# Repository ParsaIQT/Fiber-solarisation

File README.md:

# Reduced fibre solarisation in an oxygen-free atmosphere

MSc thesis project: **"Experimental demonstration of reduced fibre solarisation in an oxygen-free atmosphere"**

Thorlabs P3-375PM-FC patch cables (PM-S350-HP, pure-silica core, FC/APC) carry a few mW of 369.5 nm light
(Yb⁺ cooling and detection). They couple very well right after a fresh polish. Their throughput then
falls at a rate that grows with power, at both the input and the output end. This project tests
whether keeping the end faces in an oxygen-free atmosphere halts the degradation, using 3D-printed
enclosures with oxygen absorbers or an inert-gas purge. The experiment is designed to identify the
real cause if oxygen is not it.

## Documents

| Path | What it is |
| --- | --- |
| [`pdf/Fibre-solarisation_MSc-proposal-and-guide.pdf`](pdf/Fibre-solarisation_MSc-proposal-and-guide.pdf) | Full research proposal (Part I), student guide (Part II), appendices (design estimates, draft SOPs, logging spec), ~150 verified references |
| [`pdf/Fibre-solarisation_MSc-proposal-summary.pdf`](pdf/Fibre-solarisation_MSc-proposal-summary.pdf) | 4-page summary |
| `docs/` | LaTeX sources (`proposal.tex`, `summary.tex`, `sections/`, `figures/` in TikZ, `references.bib`, style `fsproposal.sty`) |
| `calc/estimates.py` | Design estimates quoted in Appendix A: end-face intensity, contamination flux, film thickness and heating, gas diffusion in silica, purge, permeation and absorber budgets, optics, statistics |

## Lab hardware

| Path | What it is |
| --- | --- |
| [`laser-pulse-driver/`](laser-pulse-driver/README.md) | TTL-gated 405 nm laser-diode pulse driver (BDR-209) for the photo-ionisation second step during ablation loading: KiCad schematic and 4-layer PCB with JLCPCB assembly files, 3D-printed enclosure, ngspice simulations and an ARTIQ example |

## Main points of the proposal

- **The damage is at the end faces.** Re-polishing restores the throughput, and O₂ cannot diffuse
  into silica at room temperature (nanometres per year). Any oxygen effect must therefore act at the
  surfaces.
- **The literature points both ways.** For hydrocarbon contamination of UV optics, oxygen, and often
  water, is *protective*. This holds for space lasers, UV cavities in ion-trap labs and GaN diodes.
  Under CW light at our intensity, deposits grow fastest at *trace* O₂. For siloxanes from silicones,
  O₂ ≥ 100 ppm has been found to *accelerate* deposits on a 410 nm fibre end face. Particles and
  restructuring of the silica surface itself (seen at 405 nm) are further candidates.
- **The decisive test** runs identical fibres in parallel in ambient air, clean dry synthetic air,
  clean dry N₂ and a sealed absorber cell. Only the air/N₂ pair differs in O₂ alone. Later arms add an
  O₂ dose–response, humidity, polymer and silicone challenges, and a crossed input/output design.
- **Practical outcome:** a qualified 3D-printed cell (CAD, BOM, SOPs) that holds < 100 ppm O₂ for months,
  tested on a working 369.5 nm link. If the atmosphere turns out not to be the cause, the fall-back is
  a recommendation for end-face engineering (end caps, H₂-loaded or hollow-core fibre).

## Building

Requires TeX Live (with `biber` and `latexmk`) and Python 3 (standard library only).

```sh
make            # builds both PDFs into pdf/
make estimates  # prints the numbers used in Appendix A
make clean
```

The `docs/` folder can also be uploaded to Overleaf as is (compiler: pdfLaTeX, bibliography: Biber).

## Status

Version 1.0 (18 October 2026): draft for discussion between the supervisor and the student. Names are
placeholders. Prices are US list prices or rough estimates; replace them with quotes.

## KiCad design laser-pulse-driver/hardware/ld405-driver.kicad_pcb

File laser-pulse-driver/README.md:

# LD405 – pulsed driver for a 405 nm (BDR-209) photo-ionisation laser diode

A bench-top, TTL-gated constant-current driver for a 405 nm laser diode used as
the second (ionising) step of a two-photon REMPI scheme during ablation loading.
An ARTIQ TTL line switches the diode between a low *idle* current (adjustable
5–104 mA: below threshold, or just above it for a dim alignment beam) and a
*pulse* current (adjustable 0–600 mA, or 0–700 mA with jumper JP1) for as long
as the TTL is high, e.g. 100 µs per ablation shot.

| | |
|---|---|
| Output | high-side current source, diode cathode at ground (Thorlabs "CG" DB9 pin-out) |
| Pulse current | 0–600 mA (PULSE knob), 0–700 mA with JP1 bridged; over-current trip at ~800 mA |
| Idle current | 5–104 mA (IDLE knob) whenever the TTL input is low or unconnected |
| Timing (simulated, 0.5–2.5 m cable) | ~0.7 µs delay, 4–6 µs 10–90 % rise, no overshoot, 1 % settled in ≤ 12 µs, ~7 µs fall |
| TTL input | BNC, 10 kΩ to ground, Schmitt trigger: high ≥ 2.0 V, low ≤ 0.5 V (≥ 0.4 V hysteresis); series 220 Ω + Schottky clamps to the rails. 3.3 V or 5 V TTL from ARTIQ (Kasli DIO-BNC / DIO-SMA) works directly |
| Monitors | I MON (measured diode current) and SET MON (pulse setpoint), both 1 V/A into high impedance (0.5 V/A into 50 Ω) |
| Compliance | ≥ 7 V across the diode at 700 mA (BDR-209 needs ~5–6 V) |
| Protection | output shorted by a relay and a MOSFET crowbar whenever disarmed; soft start (80 ms); over-current, open-circuit/compliance and over-temperature (85 °C) trips; two interlocks (3.5 mm jack + DB9 loop); fault latch that needs a deliberate re-arm; no auto-start after power-up |
| Supply | 9 V DC, ≥ 1.5 A (5.5/2.1 mm plug, centre positive); reverse-polarity, over-voltage and PTC fuse protection |
| Board / box | 160 × 100 mm 4-layer PCB (Eurocard), 3D-printed case 181 × 108 × 32 mm |

Design notes, simulation results and the protection logic are in
[docs/design-notes.md](docs/design-notes.md); the ARTIQ example is in
[artiq/ld405_pulse.py](artiq/ld405_pulse.py).

> **Class 4 laser.** A BDR-209 at these currents emits close to 1 W at 405 nm.
> Wear OD ≥ 4 eyewear rated for 405 nm whenever the diode is connected and
> armed, enclose the beam path, and use the interlock inputs (see *Safety*).

---

## 1. What to order, and where (UK)

Everything below ships to the UK. JLCPCB adds UK VAT at checkout for orders
up to £135; above that the courier (DHL/UPS) collects import VAT on delivery.

### 1.1 Assembled boards – JLCPCB (jlcpcb.com)

Upload these three files from [`hardware/fab/`](hardware/fab/):

| JLCPCB field | file |
|---|---|
| Gerber file (PCB order) | `ld405-driver_gerbers_jlcpcb.zip` |
| BOM (PCB Assembly step) | `ld405-driver_bom_jlcpcb.csv` |
| CPL / pick-and-place | `ld405-driver_cpl_jlcpcb.csv` |

PCB options (everything else at default):

* Layers **4**, dimensions 160 × 100 mm (read from the Gerbers), thickness **1.6 mm**,
  outer copper 1 oz, inner 0.5 oz, any colour, surface finish *LeadFree HASL*
  (or *ENIG* for the flattest pads; leaded HASL also works but puts lead on the board).
* Via covering: *Plugged* (JLCPCB no longer offers *Tented* on 4-layer boards;
  plugged vias are covered just the same, which is what the design needs).
  Min via hole size: *0.3 mm (0.4/0.45 mm)*; the board's vias are 0.3 mm drill, 0.6 mm pad.
* Quantity: 5 boards, of which **2 assembled** (one spare).

The price shown at this point covers the bare boards only. Parts and assembly
are priced after the next step.

PCB Assembly options (switch on *PCB Assembly* below *Advanced Options*):

* **Standard PCBA**, assemble **top side** only, PCBA quantity **2**, tooling
  holes added by JLCPCB. The connectors, pots and the toggle switch are
  through-hole; JLCPCB hand-solders them as part of Standard PCBA. Confirm
  *"Parts placement"* so an engineer checks it.
* Click *Next*, upload the BOM and CPL, check that every line matched a part,
  then *Next* to the placement preview; the final price (parts, assembly,
  extended-part fees) appears after that.
* After the BOM/CPL upload JLCPCB shows a placement preview. Check that the
  pin-1/polarity marks agree for: U1–U14, Q1–Q11, diodes D1–D16, the LEDs
  (D3, D8, D12, D16 – lenses must face the board edge), C1/C2 (electrolytic)
  and K1. The CPL already contains the usual KiCad→JLC rotation offsets
  (SOT-23 +180°, SOIC +270°, electrolytics +180°), offsets for the panel
  parts (BNCs +90°, pots, toggle and DE-9 +270°) and per-part corrections
  found in the preview (C1/C2, K1, Q2, D10). Compare the pink markers with
  `docs/review/jlc_markers_overview.png`. In the 3D preview the BNC
  bayonets, pot shafts and toggle lever must stick out over the front edge,
  and the DE-9, 3.5 mm jack and DC jack must open over the rear edge; rotate
  anything that still looks wrong.
* All 69 BOM lines were in stock at JLCPCB/LCSC on 28 Oct 2026 (32 are
  "extended" parts, which carry JLCPCB's per-part setup fee). Expect roughly
  £200–300 for 2 assembled boards + 3 bare boards including shipping; the
  parts themselves are ~£25 per board.
* JP1 (700 mA range) is a solder jumper and is **left open** by JLCPCB.

### 1.2 Enclosure – 3D print (JLC3DP, any UK print service, or in-house)

STL files in [`enclosure/stl/`](enclosure/stl/), already in print orientation:

| file | qty | notes |
|---|---|---|
| `ld405_base.stl` | 1 | floor, side walls, PCB standoffs, lid posts |
| `ld405_lid.stl` | 1 | printed top-side down (engraved laser warning) |
| `ld405_front_panel.stl` | 1 | BNC/pot/switch/LED holes, engraved labels |
| `ld405_rear_panel.stl` | 1 | DB9, interlock jack and DC jack |

* **JLC3DP** (same JLCPCB account, "3D Printing" tab): *MJF PA12 nylon*
  (black) is strong, dimensionally accurate and needs no tuning. Add it to the
  PCB order to share shipping. Its thin-wall heatmap should show nothing under
  1.2 mm except inside the engraved lettering (the narrow ridges between
  letters), which is normal for engraved text.
* UK alternatives: Protolabs (Telford, MJF/SLS), 3DPrintUK (London, SLS nylon),
  or the Craftcloud marketplace.
* In-house FDM: PETG or ASA, 0.2 mm layers, 4 perimeters, 30 % infill, no
  supports needed. Bed ≥ 185 × 110 mm.

The OpenSCAD source [`enclosure/ld405_enclosure.scad`](enclosure/ld405_enclosure.scad)
is generated from the board placement (`tools/gen_enclosure.py`), so the
holes follow the connectors if the layout changes.

### 1.3 Power supply and parts from RS Components / Farnell / CPC

| item | part | notes |
|---|---|---|
| 9 V DC supply | **Mean Well GST25A09-P1J** (9 V, 2.5 A, 5.5/2.1 mm plug, centre +) | desktop adapter with an IEC C14 inlet; any 9 V ≥ 1.5 A regulated supply with a 5.5/2.1 mm centre-positive plug works. RS, Farnell and CPC all stock it. |
| mains lead | UK plug → IEC C13 ("kettle lead"), 2 m | the 240 V socket within 2 m is enough |
| DB9 plug for the diode cable | DE-9 **male** solder-cup plug + metal hood with 4-40 jack screws | e.g. Amphenol/TE/Harting, any brand |
| diode cable | 2-core screened cable or a twisted pair, ≤ 2.5 m | keep the pair twisted to the diode |
| interlock plug | 3.5 mm **mono** jack plug | shorting plug, or wired to a door/enclosure interlock |
| knobs | 2 × knob for **6 mm D (flatted) shaft**, 15 mm shaft length | |
| screws | 4 × M3×16 countersunk + 4 × M3 nut (PCB); 4 × M3×10 countersunk + 4 × M3 nut (lid) | stainless A2 |
| feet | 4 × self-adhesive rubber feet, ≤ 10 mm diameter | |

The BNC nuts and washers come with the connectors; the pots normally come with
an M9×0.75 nut and washer (buy two if not).

### 1.4 Laser diode – DTR's Laser Shop

* *900 mW 405 nm Blu-ray BDR-209 laser diode in copper module with leads*
  (optionally with the *G-2 glass lens* for collimation). DTR does not publish
  a datasheet; users report ~0.8–1 W at ~500–650 mA with ~5–6 V forward
  voltage, which this driver covers with margin. Calibrate the power yourself
  (section 4).
* Clamp the copper module in a heat-sinking holder. The diode case must not be
  connected to anything except through the DB9 cable.

### 1.5 Laser safety

Eyewear rated OD ≥ 4 at 405 nm for every person in the room (Thorlabs,
Laservision, Uvex and others sell suitable orange/amber filters), plus a beam
enclosure and beam dumps appropriate for a Class 4 source.

---

## 2. Assembly (about 30 minutes)

1. **Diode cable.** Solder the DE-9 male plug: **pin 8 → diode anode (+, red)**,
   **pin 3 → diode cathode (−, black)**, and a **wire link from pin 1 to pin 5**
   inside the hood (cable interlock: unplugging the cable trips the driver).
   Screen (if any) to pin 3 at the driver end only.
2. **Interlock plug.** Short tip to sleeve in a 3.5 mm mono plug, or wire it
   to normally-closed contacts of your enclosure/door interlock.
3. **Enclosure.** Push 4 × M3 nuts into the side slots at the tops of the
   lid posts. Fit the front panel onto the board (BNC nuts and washers on the
   outside; pot nuts on the outside, the pot's small anti-rotation lug sits in
   the notch below its hole), and the rear panel over the DB9 shell. Lower
   board + panels into the base so the panels drop into their grooves, then fix
   the board with 4 × M3×16 countersunk screws from below and nuts on top.
   Fit the knobs, put the lid on, 4 × M3×10 countersunk screws.

The ENABLE toggle is held by the board only (its bushing just passes through
the panel), so operate it gently.

---

## 3. Front and rear panel

| front | function |
|---|---|
| **TTL IN** (BNC) | high = pulse current, low/unconnected = idle current |
| **I MON** (BNC) | measured diode current, 1 V/A (high-Z scope input) |
| **SET MON** (BNC) | pulse setpoint, 1 V/A – shows what a pulse will deliver before you fire |
| **PULSE** | pulse current 0 → full scale (600 mA, or 700 mA with JP1) |
| **IDLE** | idle current 5 → 104 mA |
| **ENABLE** | arm / disarm, and reset after a fault (toggle off → on) |
| LEDs | POWER (green) · ARMED (yellow: relay open, current source enabled) · EMISSION (blue: diode current > ~18 mA, stretched so 100 µs pulses are visible) · FAULT (red, latched) |

| rear | |
|---|---|
| **LD OUT** (DE-9 female) | 8 = anode, 3 = cathode/ground, 1–5 = interlock loop (Thorlabs CG compatible) |
| **INTERLOCK** (3.5 mm) | must be closed (tip–sleeve shorted) to arm |
| **9V DC** | 9 V, ≥ 1.5 A, centre positive |

Arming sequence: after power-up the driver is always in FAULT (no automatic
start). With both interlocks closed, switch ENABLE off → on: the relay opens
the output short, ~20 ms later the current source starts and ramps to the idle
current over ~80 ms. Any fault (over-current, open diode/compliance,
over-temperature, interlock open) immediately shorts and crowbars the output
and latches FAULT until ENABLE is switched off and on again.

---

## 4. First power-up and calibration

1. **Without the diode**: plug in the DB9 cable with a **dummy load** instead
   of the diode – e.g. 5 × 1N5408 (or 1N4007) in series plus a 1 Ω 2 W
   resistor (≈ 5–6 V at 0.6 A, like the laser diode; pulsed use only) – and
   the interlock plug. Turn both knobs fully anticlockwise.
2. Power up: POWER on, FAULT on. ENABLE off → on: ARMED on, FAULT off.
3. Scope on I MON (1 V/A). Turn IDLE: the trace moves between ~5 and ~104 mV.
4. Drive TTL IN with 100 µs pulses at ≤ 10 Hz (section 5). Turn PULSE up:
   I MON shows the pulses; SET MON shows the level a pulse will reach.
   Check the pulse at full scale (≈ 600 mV on I MON) is flat with no ringing.
5. Optional 700 mA range: bridge solder jumper **JP1** (near U2/REF3030).
6. Disconnect one lead of the dummy load at the far end, leaving the DB9
   plugged in: FAULT must latch (open-circuit detection). Unplugging the DB9
   itself must also latch FAULT (cable interlock). Set both knobs to minimum,
   **disarm**, connect the diode, then arm.
7. Calibrate optical power with a thermal power meter: at a known duty cycle
   *D* the meter reads *P̄ ≈ P_peak · D* (e.g. 100 µs at 100 Hz, D = 1 %), or
   use a fast photodiode for the pulse shape. Increase PULSE slowly; read the
   current on I MON and note the knob position for your target peak power
   (~900 mW). Do not exceed the diode's current rating.

Duty cycle: the driver itself is fine at any duty cycle up to a few % at full
current (the pass transistor is heat-sunk into the board and the 85 °C
trip protects it); limit the duty cycle further for the diode's sake.

---

## 5. Using it from ARTIQ

Connect a Kasli TTL output (DIO-BNC/-SMA) to **TTL IN**. TTL high = pulse.
The current needs ~1 µs to start rising and ~10 µs to settle to 1 %, so open
the pulse ~10–15 µs before you need full power. [`artiq/ld405_pulse.py`](artiq/ld405_pulse.py)
fires the ablation trigger inside a 100 µs 405 nm pulse:

```python
with parallel:
    self.ttl_ld405.pulse(self.pulse_width)          # 405 nm REMPI 2nd step
    with sequential:
        delay(self.lead)                            # ~15 us head start
        self.ttl_ablation.pulse(self.ablation_width)
```

Tip: setting IDLE just above threshold gives a dim continuous 405 nm beam for
aligning onto the trap without firing pulses.

---

## 6. Repository layout

| path | contents |
|---|---|
| `hardware/` | KiCad 9 project: schematic, 4-layer PCB, custom footprints (`lib/ld405.pretty`) |
| `hardware/fab/` | manufacturing outputs (Gerbers, BOM, CPL), schematic + assembly PDFs, renders |
| `enclosure/` | OpenSCAD source, STL files, preview images |
| `artiq/` | ARTIQ experiment for ablation loading with the pulsed 405 nm laser |
| `sim/` | ngspice testbench and corner simulations (`get_models.sh` fetches the vendor models) |
| `docs/` | design notes, simulation plots and the design-review renders (`docs/review/`) |
| `review_package/` | for an outside reviewer: `LD405_design_review.pdf` (design review document with schematic) and `LD405_review_pack.zip` (that PDF plus KiCad project, JLCPCB files, layer plots, ERC/DRC reports, simulation, enclosure and review renders) |
| `tools/` | the generators: everything in `hardware/`, `hardware/fab/` and `enclosure/` is produced by these scripts |

Regenerating from source (KiCad 9 with its Python module, numpy, scipy, poppler,
matplotlib, gcc, OpenSCAD, ngspice):

```sh
cd tools
python3 gen_3d.py              # simple 3D models for parts without a KiCad model
python3 gen_fp.py              # custom footprints
python3 gen_sch.py             # schematic (ERC clean)
python3 gen_pcb.py --route     # placement, routing, zones, DRC-clean board
python3 export_fab.py          # Gerbers, drill, BOM, CPL, PDFs, renders
python3 gen_enclosure.py       # OpenSCAD model and STLs
python3 review.py              # review renders in docs/review/
cd ../sim && ./get_models.sh && python3 run_sims.py
cd ../tools && python3 make_review_pack.py   # review_package/ (needs node + Playwright for the PDF)
```

`design.py` is the single source of truth for parts, values, LCSC numbers and
connections; `placement.py` holds the component positions.

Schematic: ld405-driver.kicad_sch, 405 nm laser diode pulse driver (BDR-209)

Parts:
C1, C2: 220uF 25V; CP_Elec_8x10.5; MPN RVT1E221M0810; LCSC C72497
C3, C4, C7, C11: 10uF; C_0805_2012Metric; MPN CL21A106KAYNNNE; LCSC C15850
C5, C8, C13, C14, C16, C17, C18, C20, C21, C22, C23, C24, C25, C26, C34, C40, C41: 100nF; C_0603_1608Metric; MPN CC0603KRX7R9BB104; LCSC C14663
C6, C9, C10, C19: 1uF; C_0603_1608Metric; MPN CL10A105KB8NNNC; LCSC C15849
C12, C31: 220pF C0G; C_0603_1608Metric; MPN GCM1885C2A221JA16D; LCSC C388907
C15, C30, C33: 100pF C0G; C_0603_1608Metric; MPN CL10C101JB8NNNC; LCSC C14858
C32: 47nF; C_0603_1608Metric; MPN CL10B473KB8NNNC; LCSC C1622
C42: 10nF; C_0603_1608Metric; MPN 0603B103K500NT; LCSC C57112
C43: 2.2uF; C_0603_1608Metric; MPN CL10A225KO8NNNC; LCSC C23630
C44: 1nF; C_0603_1608Metric; MPN CL10B102KB8NNNC; LCSC C1588
C45: 220nF; C_0603_1608Metric; MPN CL10B224KA8NNNC; LCSC C21120
D1: BZT52C10; D_SOD-123; MPN BZT52C10; LCSC C19077408
D2: SMAJ13A; D_SMA; MPN SMAJ13A; LCSC C19077533
D3: POWER green; LED_SideView_LiteOn_LTST-S220; MPN LTST-S220TGKT; LCSC C160470
D4: BAT54S; SOT-23; MPN BAT54S; LCSC C7420333
D5, D13, D14, D15: 1N4148WS; D_SOD-323; MPN 1N4148WS; LCSC C2128
D6: SS34; D_SMA; MPN SS34; LCSC C8678
D7: SMAJ12A; D_SMA; MPN SMAJ12A; LCSC C19077531
D8: EMISSION blue; LED_SideView_LiteOn_LTST-S220; MPN LTST-S220TBKT; LCSC C160471
D10: BAT54A; SOT-23; MPN BAT54A; LCSC C7502690
D12: FAULT red; LED_SideView_LiteOn_LTST-S220; MPN LTST-S220KRKT; LCSC C284935
D16: ARMED yellow; LED_SideView_LiteOn_LTST-S220; MPN LTST-S220KSKT; LCSC C160468
F1: 2A PTC; Fuse_1812_4532Metric; MPN BSMD1812-200-30V; LCSC C960026
H1, H2, H3, H4: M3; MountingHole_3.2mm_M3_Pad_Via
J1: 9V DC IN; BarrelJack_DC-005_Horizontal; MPN DC-005-5A-2.0; LCSC C381116
J2: TTL IN; BNC_DOSIN_801-0080_Horizontal; MPN DOSIN-801-0080; LCSC C521219
J3: SET MON; BNC_DOSIN_801-0080_Horizontal; MPN DOSIN-801-0080; LCSC C521219
J4: I MON; BNC_DOSIN_801-0080_Horizontal; MPN DOSIN-801-0080; LCSC C521219
J5: LD OUT; DSUB-9_Socket_Horizontal_P2.77x2.84mm_EdgePinOffset7.70mm_H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; MPN DS1037-09FNAKT74-0CC; LCSC C75749
J6: INTERLOCK; Jack_3.5mm_KoreanHropartsElec_PJ-320D-4A_Horizontal; MPN PJ-320D; LCSC C431535
JP1: I_MAX 700mA; SolderJumper-2_P1.3mm_Open_RoundedPad1.0x1.5mm
K1: G6K-2F-Y 5V; Relay_DPDT_Omron_G6K-2F-Y; MPN G6K-2F-Y-TR DC5; LCSC C47190
NT1, NT2: NetTie; NetTie-2_SMD_Pad0.5mm
Q1, Q6, Q7, Q11: AO3401A; SOT-23; MPN AO3401A; LCSC C15127
Q2: IRFR9024N; TO-252-2; MPN IRFR9024NTRPBF; LCSC C2585
Q3, Q4, Q5, Q8, Q9: 2N7002; SOT-23; MPN 2N7002; LCSC C8545
Q10: AO3400A; SOT-23; MPN AO3400A; LCSC C20917
R1, R15, R36, R37, R39, R43, R53, R54, R59, R78, R79: 100k; R_0603_1608Metric; LCSC C25803
R2: 2.2k; R_0603_1608Metric; LCSC C4190
R10: 10k 0.1%; R_0603_1608Metric; MPN RT0603BRD0710KL; LCSC C95204
R11: 40.2k 0.1%; R_0603_1608Metric; MPN TD03G4022BT; LCSC C667101
R12: 4.02k; R_0603_1608Metric; LCSC C23040
R13, R30, R34, R42: 100; R_0603_1608Metric; LCSC C22775
R16, R17, R33, R62, R81, R82: 1k; R_0603_1608Metric; LCSC C21190
R18, R31, R45: 3k 0.1%; R_0603_1608Metric; MPN RT0603BRD073KL; LCSC C136963
R19, R46: 1k 0.1%; R_0603_1608Metric; MPN RT0603BRD071KL; LCSC C110776
R20, R47: 49.9; R_0603_1608Metric; LCSC C23185
R21: 220; R_0603_1608Metric; LCSC C22962
R22, R35, R50, R56, R70, R73: 10k; R_0603_1608Metric; LCSC C25804
R32: 150 0.1%; R_0603_1608Metric; MPN AR03BTCX1500; LCSC C319859
R38, R48: 47k; R_0603_1608Metric; LCSC C25819
R40: 0.2; R_2512_6332Metric; MPN RLP25FEER200; LCSC C459674
R41: 1.0; R_2512_6332Metric; MPN 25121WF100KT4E; LCSC C11254
R44: 22; R_0805_2012Metric; LCSC C17561
R51: 18k; R_0603_1608Metric; LCSC C25810
R52: 300k; R_0603_1608Metric; LCSC C23024
R55: 11k; R_0603_1608Metric; LCSC C25950
R60: 1.5k; R_0603_1608Metric; LCSC C22843
R61: 1M; R_0603_1608Metric; LCSC C22935
R72: 4.7k; R_0603_1608Metric; LCSC C23162
R77: 3.3k; R_0603_1608Metric; LCSC C22978
RT1: 10k B3950; R_0603_1608Metric; MPN SDNT1608X103F3950FTF; LCSC C279936
RV1: PULSE 20k; Potentiometer_Alps_RK09L_Single_Horizontal; MPN RK09L112003P; LCSC C470444
RV2: IDLE 20k; Potentiometer_Alps_RK09L_Single_Horizontal; MPN RK09L112003P; LCSC C470444
SW1: ENABLE; Toggle_Dailywell_1MS1T2B4M7QES; MPN 1MS1T2B4M7QES; LCSC C496157
U1: L78M05ABDT; TO-252-2; MPN L78M05ABDT-TR; LCSC C58069
U2: REF3030; SOT-23; MPN REF3030AIDBZR; LCSC C38423
U3, U4, U10: TLV9062; SOIC-8_3.9x4.9mm_P1.27mm; MPN TLV9062IDR; LCSC C398355
U5: SN74LVC1G3157; SOT-23-6; MPN SN74LVC1G3157DBVR; LCSC C10426
U7: OPA2192; SOIC-8_3.9x4.9mm_P1.27mm; MPN OPA2192IDR; LCSC C110074
U8: INA180A1; SOT-23-5; MPN INA180A1IDBVR; LCSC C122228
U11: LM2901; SOIC-14_3.9x8.7mm_P1.27mm; MPN LM2901DR; LCSC C7932
U12: 74HC14; SOIC-14_3.9x8.7mm_P1.27mm; MPN 74HC14D; LCSC C5605
U13: 74HC132; SOIC-14_3.9x8.7mm_P1.27mm; MPN SN74HC132DR; LCSC C350560
U14: 74AHCT1G14; SOT-23-5; MPN SN74AHCT1G14DBVR; LCSC C55250

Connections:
+5V: C7.1, C8.1, C10.1, C13.1, C14.1, C16.1, C17.1, C20.1, C21.1, C22.1, C25.1, C26.1, D4.2 (K), D5.1 (K), D13.1 (K), K1.1, Q11.2 (S), R2.1, R50.1, R54.1, R56.1, R59.1, R61.1, R70.1, R72.1, R73.1, R77.1, R78.1, U1.3 (VO), U2.1 (IN), U3.8 (V+), U4.8 (V+), U5.5 (VCC), U8.5 (V+), U10.8 (V+), U11.3 (V+), U12.14 (VCC), U13.14 (VCC), U14.5 (VCC)
CB_G: Q10.1 (G), R42.2, R43.1
CLAMP_G: Q6.1 (G), Q7.3 (D), R37.2, R38.1
CMP_REF: C23.1, R54.2, R55.1, U11.6 (-), U11.10 (-)
DB9_IL: C42.1, J5.1, R77.2, U12.5
DB9_OK: D10.2, U12.6
DIS_LOOP: Q3.1 (G), Q5.1 (G), R42.1, U12.8, U12.11
EA_N: C31.1, R33.2, R36.2, U7.2 (-)
EA_OUT: C31.2, R34.1, U7.1
EMI_RC: C34.1, Q11.1 (G), R61.2, U11.14
EM_REF: R59.2, R60.1, U11.9 (+)
EN_DLY: C45.1, D15.2 (A), R79.2, U12.9
EN_LOOP: Q8.1 (G), U12.10
EN_ON: U12.2, U13.4, U13.9
EN_REQ: D15.1 (K), Q9.1 (G), R79.1, R82.1, U13.11
EN_REQ_N: U13.8, U13.12, U13.13
EN_SW: C40.1, R70.2, SW1.1 (A), U12.1
FAULT: R81.1, U13.3, U13.5
FAULT_N: U13.2, U13.6, U13.10
GATE: Q2.1 (G), Q6.3 (D), R34.2, R35.1, R52.1
GATE_N: U5.6, U14.4
GND: C1.2, C2.2, C3.2, C4.2, C5.2, C6.2, C7.2, C8.2, C9.2, C10.2, C11.2, C12.2, C13.2, C14.2, C15.2, C16.2, C17.2, C18.2, C19.2, C20.2, C21.2, C22.2, C23.2, C24.2, C25.2, C26.2, C32.2, C33.2, C34.2, C40.2, C41.2, C42.2, C43.2, C44.2, C45.2, D2.2 (A2), D3.1 (K), D4.1 (A), D6.2 (A), D7.2 (A2), D8.1 (K), D12.1 (K), D16.1 (K), H1.1, H2.1, H3.1, H4.1, J1.2, J1.3, J2.2 (Ext), J3.2 (Ext), J4.2 (Ext), J5.0 (PAD), J5.3, J5.5, J6.S, K1.2, K1.7, Q3.2 (S), Q5.2 (S), Q8.2 (S), Q9.2 (S), Q10.2 (S), R1.2, R11.2, R16.2, R19.2, R22.2, R31.2, R38.2, R43.2, R46.2, R51.2, R53.2, R55.2, R60.2, RT1.2, RV1.1, SW1.2 (B), U1.2 (GND), U2.3 (GND), U3.4 (V-), U4.4 (V-), U5.2 (GND), U7.4 (V-), U8.2 (GND), U10.4 (V-), U10.5 (+), U11.12 (V-), U12.7 (GND), U12.13, U13.7 (GND), U14.3 (GND)
G_DIV: C33.1, R52.2, R53.1, U11.7 (+)
IDLE_BOT: R16.1, RV2.1
IDLE_TOP: R15.2, RV2.3
IMON: J4.1 (In), R47.2
IMON_INT: R45.1, U8.1, U11.4 (-), U11.8 (-)
IMON_OUT: R47.1, U10.1, U10.2 (-)
IM_DIV: R45.2, R46.1, U10.3 (+)
JP1_B: JP1.2 (B), R12.1
LD_OUT: D6.1 (K), D7.1 (A1), J5.8, K1.3, K1.6, Q2.2 (D), Q10.3 (D), R44.1
LED_ARM: D16.2 (A), R82.2
LED_EMI: D8.2 (A), R62.2
LED_FLT: D12.2 (A), R81.2
LED_PWR: D3.2 (A), R2.2
LS_G: Q4.1 (G), R30.2
LS_GO: R30.1, U7.7
LS_S: Q4.2 (S), R31.1, U7.6 (-)
NTC_N: C24.1, R56.2, RT1.1, U11.11 (+)
OC_REF: R50.2, R51.1, U11.5 (+)
POR_RC: C43.1, D13.2 (A), D14.1 (K), R78.2
Q1_G: D1.2 (A), Q1.1 (G), R1.1
Q5_D: Q5.3 (D), R36.1
Q8_D: Q8.3 (D), R48.2
Q11_D: Q11.3 (D), R62.1
REF_N: C30.2, Q4.3 (D), R32.2, U7.3 (+)
REL_G: Q7.1 (G), R39.2, R48.1
REM_N: C41.1, J6.T, R72.2, U12.3
REM_OK: D10.1, U12.4
RLY_N: D5.2 (A), K1.8, Q9.3 (D)
SETMON: J3.1 (In), R20.2
SETMON_OUT: R20.1, U4.6 (-), U4.7
SM_DIV: R18.2, R19.1, U4.5 (+)
SNUB: C32.1, R44.2
SRC_D: Q2.3 (S), R41.2
SRC_K: NT2.1, R40.2, R41.1
SRC_SNS: NT2.2, R33.1, U8.4 (-)
SS_D: Q3.3 (D), R13.1
S_N: C44.1, D10.3, D14.2 (A), R73.2, U11.1, U11.2, U11.13, U13.1
TTL_BNC: J2.1 (In), R21.1, R22.1
TTL_PROT: C15.1, D4.3 (COM), R21.2, U14.2
U10B_OUT: U10.6 (-), U10.7
VFS: R15.1, RV1.3, U3.1, U3.2 (-)
VFS_RAW: C11.1, R10.2, R11.1, R12.2, R13.2, U3.3 (+)
VI: U4.1, U4.2 (-), U5.1
VIN: C1.1, C2.1, C3.1, C4.1, C5.1, C6.1, C18.1, C19.1, D1.1 (K), D2.1 (A1), NT1.1, Q1.2 (S), Q6.2 (S), Q7.2 (S), R35.2, R37.1, R39.1, R40.1, U1.1 (VI), U7.8 (V+)
VIN_F: F1.2, Q1.3 (D)
VIN_RAW: F1.1, J1.1
VIN_SNS: C30.1, NT1.2, R32.1, U8.3 (+)
VI_W: RV2.2, U4.3 (+)
VP: R18.1, U3.6 (-), U3.7, U5.3
VP_W: RV1.2, U3.5 (+)
VREF: C9.1, JP1.1 (A), R10.1, U2.2 (OUT)
VSP: C12.1, R17.2, U7.5 (+)
VSP_MUX: R17.1, U5.4

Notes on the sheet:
1 POWER INPUT, 5 V AND 3.000 V REFERENCE
9 V / >=1.5 A desktop adapter (5.5/2.1 mm, centre +).
Q1 = reverse-polarity protection, F1 = resettable fuse, D2 = TVS.
2 SETPOINT, SOFT START AND TTL GATING (scale 4 V/A)
VFS = 2.40 V = 600 mA full scale (JP1 closed: 2.80 V = 700 mA).
C11 + R10||R11 give an 80 ms soft start; Q3 discharges it when disabled.
U5 selects PULSE (TTL high) or IDLE (TTL low, 5..104 mA).
3 TTL INPUT (BNC, 10 k to GND, 3.3/5 V logic)
Schmitt trigger with TTL thresholds; unconnected input = IDLE.
4 HIGH-SIDE CURRENT SOURCE (laser cathode at GND)
I_LD = VSP x (R32/R31) / R40 = VSP / 4 V/A.
U7A error amp senses R40 directly (Kelvin via NT1/NT2); R41 degenerates Q2.
Q6 clamps Q2 off unless EN_LOOP is high (fail-safe, Q7/Q8 release it).
Q5 forces U7A high while disabled so the integrator cannot wind up.
5 OUTPUT, SHORTING RELAY AND CROWBAR
K1 NC contacts short the laser whenever the driver is not armed or unpowered.
Q10 crowbar shorts it within 1 us of a fault; D6/D7 reverse and surge clamp.
DB9 follows Thorlabs LD-driver 'CG' pinout: 8 = anode, 3 = cathode/GND, 1-5 interlock.
6 CURRENT AND SETPOINT MONITORS (1 V/A into high-Z)
I MON from INA180 (4 V/A) / 4; SET MON shows the PULSE setpoint / 4.
7 PROTECTION COMPARATORS
A: over-current > 800 mA. B: compliance / open laser (gate < 2 V for > 10 us).
C: Q2 heatsink > 85 C (NTC RT1). D: emission > 19 mA lights the EMISSION LED for ~0.15 s.
8 INTERLOCKS, FAULT LATCH AND ENABLE SEQUENCING
Any fault, open interlock or power-up sets the FAULT latch; reset by switching ENABLE off.
EN_REQ arms relay K1 at once; EN_LOOP releases the current source ~17 ms later.
9 FRONT-PANEL INDICATORS
10 IC POWER PINS
11 MOUNTING HOLES

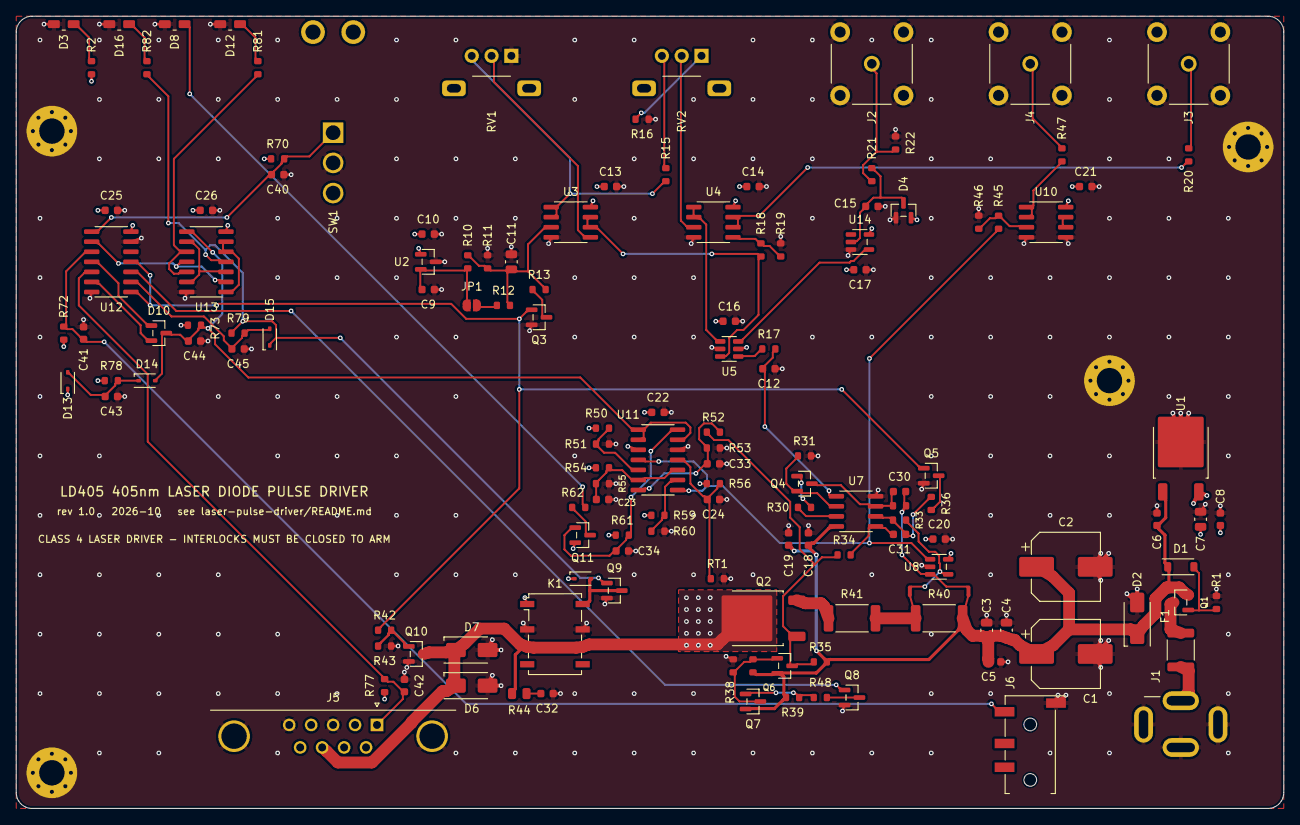
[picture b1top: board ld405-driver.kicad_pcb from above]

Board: 4 copper layers, 160.0 x 100.0 mm, 145 parts (0 on the bottom side), 75 nets.

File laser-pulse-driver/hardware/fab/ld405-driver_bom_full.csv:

Qty,Value,Designators,Footprint,Manufacturer part,LCSC
2,220uF 25V,C1 C2,CP_Elec_8x10.5,RVT1E221M0810,C72497
4,10uF,C3 C4 C7 C11,C_0805_2012Metric,CL21A106KAYNNNE,C15850
17,100nF,C5 C8 C13 C14 C16 C17 C18 C20 C21 C22 C23 C24 C25 C26 C34 C40 C41,C_0603_1608Metric,CC0603KRX7R9BB104,C14663
4,1uF,C6 C9 C10 C19,C_0603_1608Metric,CL10A105KB8NNNC,C15849
2,220pF C0G,C12 C31,C_0603_1608Metric,GCM1885C2A221JA16D,C388907
3,100pF C0G,C15 C30 C33,C_0603_1608Metric,CL10C101JB8NNNC,C14858
1,47nF,C32,C_0603_1608Metric,CL10B473KB8NNNC,C1622
1,10nF,C42,C_0603_1608Metric,0603B103K500NT,C57112
1,2.2uF,C43,C_0603_1608Metric,CL10A225KO8NNNC,C23630
1,1nF,C44,C_0603_1608Metric,CL10B102KB8NNNC,C1588
1,220nF,C45,C_0603_1608Metric,CL10B224KA8NNNC,C21120
1,BZT52C10,D1,D_SOD-123,BZT52C10,C19077408
1,SMAJ13A,D2,D_SMA,SMAJ13A,C19077533
1,POWER green,D3,LED_SideView_LiteOn_LTST-S220,LTST-S220TGKT,C160470
1,BAT54S,D4,SOT-23,BAT54S,C7420333
4,1N4148WS,D5 D13 D14 D15,D_SOD-323,1N4148WS,C2128
1,SS34,D6,D_SMA,SS34,C8678
1,SMAJ12A,D7,D_SMA,SMAJ12A,C19077531
1,EMISSION blue,D8,LED_SideView_LiteOn_LTST-S220,LTST-S220TBKT,C160471
1,BAT54A,D10,SOT-23,BAT54A,C7502690
1,FAULT red,D12,LED_SideView_LiteOn_LTST-S220,LTST-S220KRKT,C284935
1,ARMED yellow,D16,LED_SideView_LiteOn_LTST-S220,LTST-S220KSKT,C160468
1,2A PTC,F1,Fuse_1812_4532Metric,BSMD1812-200-30V,C960026
1,9V DC IN,J1,BarrelJack_DC-005_Horizontal,DC-005-5A-2.0,C381116
1,TTL IN,J2,BNC_DOSIN_801-0080_Horizontal,DOSIN-801-0080,C521219
1,SET MON,J3,BNC_DOSIN_801-0080_Horizontal,DOSIN-801-0080,C521219
1,I MON,J4,BNC_DOSIN_801-0080_Horizontal,DOSIN-801-0080,C521219
1,LD OUT,J5,DSUB-9_Socket_Horizontal_P2.77x2.84mm_EdgePinOffset7.70mm_Housed_MountingHolesOffset9.12mm,DS1037-09FNAKT74-0CC,C75749
1,INTERLOCK,J6,Jack_3.5mm_KoreanHropartsElec_PJ-320D-4A_Horizontal,PJ-320D,C431535
1,G6K-2F-Y 5V,K1,Relay_DPDT_Omron_G6K-2F-Y,G6K-2F-Y-TR DC5,C47190
4,AO3401A,Q1 Q6 Q7 Q11,SOT-23,AO3401A,C15127
1,IRFR9024N,Q2,TO-252-2,IRFR9024NTRPBF,C2585
5,2N7002,Q3 Q4 Q5 Q8 Q9,SOT-23,2N7002,C8545
1,AO3400A,Q10,SOT-23,AO3400A,C20917
11,100k,R1 R15 R36 R37 R39 R43 R53 R54 R59 R78 R79,R_0603_1608Metric,,C25803
1,2.2k,R2,R_0603_1608Metric,,C4190
1,10k 0.1%,R10,R_0603_1608Metric,RT0603BRD0710KL,C95204
1,40.2k 0.1%,R11,R_0603_1608Metric,TD03G4022BT,C667101
1,4.02k,R12,R_0603_1608Metric,,C23040
4,100,R13 R30 R34 R42,R_0603_1608Metric,,C22775
6,1k,R16 R17 R33 R62 R81 R82,R_0603_1608Metric,,C21190
3,3k 0.1%,R18 R31 R45,R_0603_1608Metric,RT0603BRD073KL,C136963
2,1k 0.1%,R19 R46,R_0603_1608Metric,RT0603BRD071KL,C110776
2,49.9,R20 R47,R_0603_1608Metric,,C23185
1,220,R21,R_0603_1608Metric,,C22962
6,10k,R22 R35 R50 R56 R70 R73,R_0603_1608Metric,,C25804
1,150 0.1%,R32,R_0603_1608Metric,AR03BTCX1500,C319859
2,47k,R38 R48,R_0603_1608Metric,,C25819
1,0.2,R40,R_2512_6332Metric,RLP25FEER200,C459674
1,1.0,R41,R_2512_6332Metric,25121WF100KT4E,C11254
1,22,R44,R_0805_2012Metric,,C17561
1,18k,R51,R_0603_1608Metric,,C25810
1,300k,R52,R_0603_1608Metric,,C23024
1,11k,R55,R_0603_1608Metric,,C25950
1,1.5k,R60,R_0603_1608Metric,,C22843
1,1M,R61,R_0603_1608Metric,,C22935
1,4.7k,R72,R_0603_1608Metric,,C23162
1,3.3k,R77,R_0603_1608Metric,,C22978
1,10k B3950,RT1,R_0603_1608Metric,SDNT1608X103F3950FTF,C279936
1,PULSE 20k,RV1,Potentiometer_Alps_RK09L_Single_Horizontal,RK09L112003P,C470444
1,IDLE 20k,RV2,Potentiometer_Alps_RK09L_Single_Horizontal,RK09L112003P,C470444
1,ENABLE,SW1,Toggle_Dailywell_1MS1T2B4M7QES,1MS1T2B4M7QES,C496157
1,L78M05ABDT,U1,TO-252-2,L78M05ABDT-TR,C58069
1,REF3030,U2,SOT-23,REF3030AIDBZR,C38423
3,TLV9062,U3 U4 U10,SOIC-8_3.9x4.9mm_P1.27mm,TLV9062IDR,C398355
1,SN74LVC1G3157,U5,SOT-23-6,SN74LVC1G3157DBVR,C10426
1,OPA2192,U7,SOIC-8_3.9x4.9mm_P1.27mm,OPA2192IDR,C110074
1,INA180A1,U8,SOT-23-5,INA180A1IDBVR,C122228
1,LM2901,U11,SOIC-14_3.9x8.7mm_P1.27mm,LM2901DR,C7932
1,74HC14,U12,SOIC-14_3.9x8.7mm_P1.27mm,74HC14D,C5605
1,74HC132,U13,SOIC-14_3.9x8.7mm_P1.27mm,SN74HC132DR,C350560
1,74AHCT1G14,U14,SOT-23-5,SN74AHCT1G14DBVR,C55250

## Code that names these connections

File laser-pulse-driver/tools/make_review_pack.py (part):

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Schmitt trigger, thresholds 0.9–2.0 V rising and 0.5–1.6 V falling) drives the switch's select line. The input is not
terminated; ARTIQ's DIO-BNC drives it directly.</p>
<h2>4.4 Current source (U7, Q2, Q4, R30–R41, NT1, NT2)</h2>
<div class="eq">VIN ── R40 0.2 Ω ──┬── R41 1.0 Ω ── S  Q2 IRFR9024N  D ── LD_OUT ── DE-9 pin 8 → diode → pin 3 ── GND
     (Kelvin NT1)  └ (Kelvin NT2)      G ← R34 100 Ω ← U7A (integrator R33 / C31)</div>
<ul>
<li><b>Level shifter</b> (U7B + Q4) forces <span class="mono">VSP</span> across R31 (3.00 k), and the same current
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<h2>5.1 Fault sources</h2>
<p>LM2901 open-collector comparators share the active-low fault line <span class="mono">S_N</span> (R73 pull-up,
C44 filter). The interlocks join <span class="mono">S_N</span> through the BAT54A D10: the 3.5 mm jack
(<span class="mono">REM_N</span>, closed = OK) and the DE-9 loop (<span class="mono">DB9_IL</span>, pins 1–5 linked
in the cable). At power-up R78/C43 hold <span class="mono">S_N</span> low for ~0.2 s through D14.</p>""")
    a(table(["source", "trips when", "threshold"], [
        ["U11A over-current", "I MON (4 V/A) &gt; <span class='mono'>OC_REF</span> 3.21 V", "804 mA"],
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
